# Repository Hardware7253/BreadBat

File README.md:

# BreadBat
A 3.3v breadbaord power supply that's powered by a single cell Li-Ion battery and uses USB-C for charging.
This design was made for prototyping portable devices on a breadboard.

I've had this designed manufactured and during testing I realised I forgot to consider the drop out voltage of the linear regulator. The battery charging and circuit protection seems to work fine, but the battery voltage isn't high enough for the LDO to reach a 3.3v output.

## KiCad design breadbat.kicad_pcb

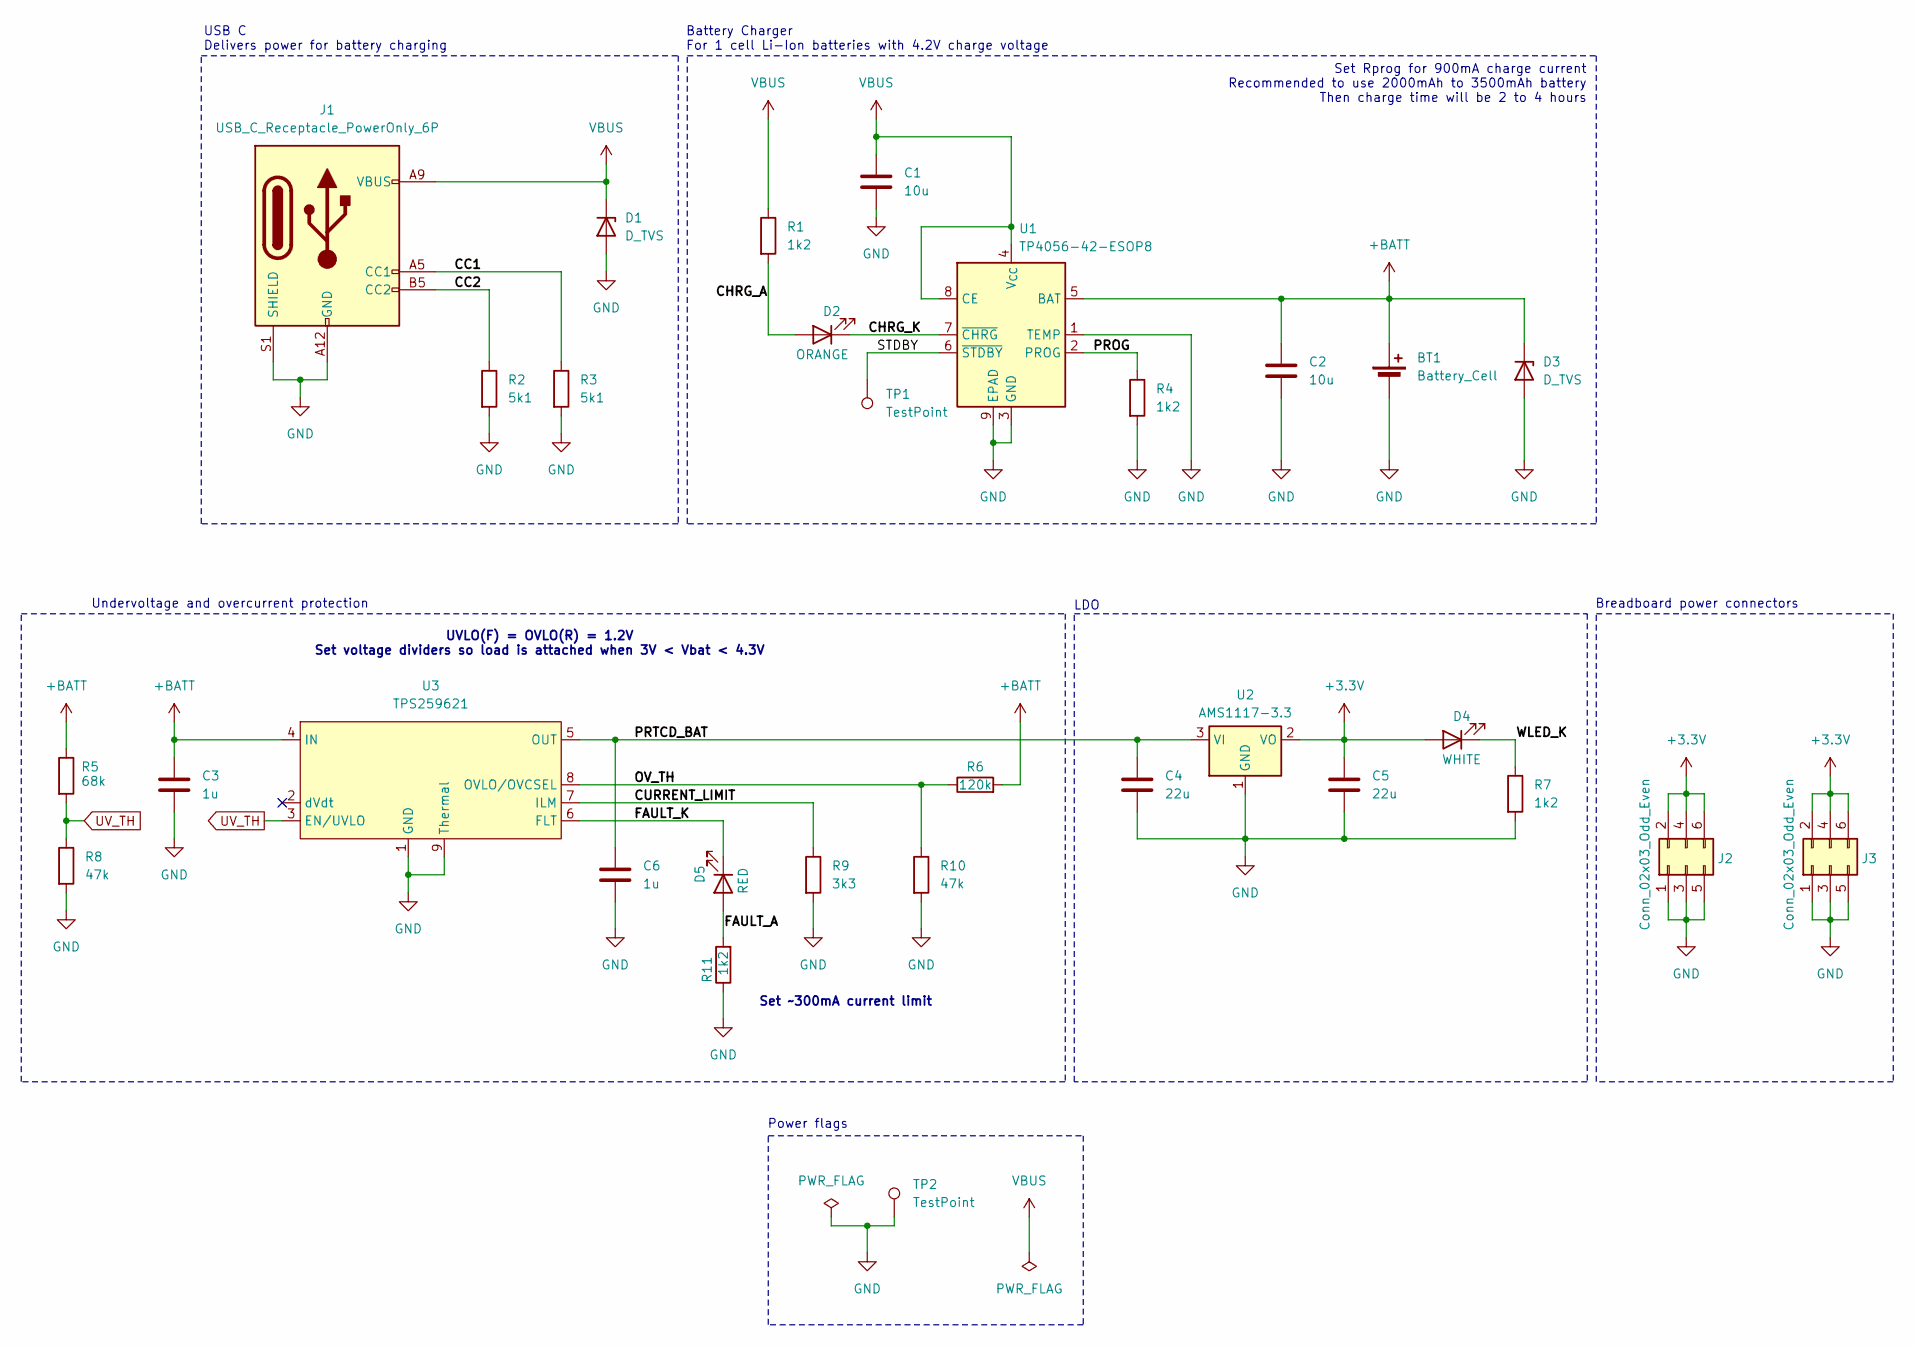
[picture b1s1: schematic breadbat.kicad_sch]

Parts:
BT1: Battery_Cell; JST_PH_B2B-PH-K_1x02_P2.00mm_Vertical; Part Number B2B-PH-K-S(LF)(SN); LCSC / JLC Part C131337
C1, C2: 10u; C_0603_1608Metric; Part Number CL10A106KP8NNNC; LCSC / JLC Part C19702
C3, C6: 1u; C_0603_1608Metric; Part Number CL10A105KB8NNNC; LCSC / JLC Part C15849
C4, C5: 22u; C_0805_2012Metric; Part Number CL21A226MAQNNNE; LCSC / JLC Part C45783
D1, D3: D_TVS; D_SOD-323_HandSoldering; Part Number WPE0731D3; LCSC / JLC Part C5143684
D2: ORANGE; LED_0603_1608Metric; Part Number KT-0603Y; LCSC / JLC Part C2287
D4: WHITE; LED_0603_1608Metric; Part Number KT-0603W; LCSC / JLC Part C2290
D5: RED; LED_0603_1608Metric; Part Number KT-0603R; LCSC / JLC Part C2286
J1: USB_C_Receptacle_PowerOnly_6P; USB_C_Receptacle_HRO_TYPE-C-31-M-17; Part Number YTC-TC6S-231; LCSC / JLC Part C2927302
J2, J3: Conn_02x03_Odd_Even; PinHeader_2x03_P2.54mm_Vertical; Part Number PZ254V-12-6P; LCSC / JLC Part C492420
R1, R4, R7, R11: 1k2; R_0603_1608Metric; Part Number 0603WAF1201T5E; LCSC / JLC Part C22765
R2, R3: 5k1; R_0603_1608Metric; Part Number 0603WAF5101T5E; LCSC / JLC Part C23186
R5: 68k; R_0603_1608Metric; Part Number 0603WAF6802T5E; LCSC / JLC Part C23231
R6: 120k; R_0603_1608Metric; Part Number 0603WAF1203T5E; LCSC / JLC Part C25808
R8, R10: 47k; R_0603_1608Metric; Part Number 0603WAF4702T5E; LCSC / JLC Part C25819
R9: 3k3; R_0603_1608Metric; Part Number 0603WAF3301T5E; LCSC / JLC Part C22978
TP1, TP2: TestPoint; TestPoint_Pad_D1.5mm
U1: TP4056-42-ESOP8; SOIC-8-1EP_3.9x4.9mm_P1.27mm_EP2.41x3.3mm_ThermalVias; Part Number TP4056-42-ESOP8; LCSC / JLC Part C16581
U2: AMS1117-3.3; SOT-223-3_TabPin2; Part Number AMS1117-3.3; LCSC / JLC Part C347222
U3: TPS259621; SOIC-8-1EP_3.9x4.9mm_P1.27mm_EP2.41x3.3mm_ThermalVias; Part Number TPS259621DDAR; LCSC / JLC Part C2155774

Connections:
+3.3V: C5.1, D4.2 (A), J2.2, J2.4, J2.6, J3.2, J3.4, J3.6, U2.2 (VO)
+BATT: BT1.1 (+), C2.1, C3.1, D3.1 (K), R5.1, R6.2, U1.5 (BAT), U3.4 (IN)
/CC1: J1.A5 (CC1), R3.1
/CC2: J1.B5 (CC2), R2.1
/CHRG_A: D2.2 (A), R1.2
/CHRG_K: D2.1 (K), U1.7 (~CHRG)
/CURRENT_LIMIT: R9.1, U3.7 (ILM)
/FAULT_A: D5.2 (A), R11.2
/FAULT_K: D5.1 (K), U3.6 (FLT)
/OV_TH: R6.1, R10.1, U3.8 (OVLO/OVCSEL)
/PROG: R4.1, U1.2 (PROG)
/PRTCD_BAT: C4.1, C6.1, U2.3 (VI), U3.5 (OUT)
/STDBY: TP1.1, U1.6 (~STDBY)
/WLED_K: D4.1 (K), R7.1
GND: BT1.2 (-), C1.2, C2.2, C3.2, C4.2, C5.2, C6.2, D1.2 (A), D3.2 (A), J1.A12 (GND), J1.B12 (GND), J1.S1 (SHIELD), J2.1, J2.3, J2.5, J3.1, J3.3, J3.5, R2.2, R3.2, R4.2, R7.2, R8.2, R9.2, R10.2, R11.1, TP2.1, U1.1 (TEMP), U1.3 (GND), U1.9 (EPAD), U2.1 (GND), U3.1 (GND), U3.9 (Thermal)
UV_TH: R5.2, R8.1, U3.3 (EN/UVLO)
VBUS: C1.1, D1.1 (K), J1.A9 (VBUS), J1.B9 (VBUS), R1.1, U1.4 (V_{CC}), U1.8 (CE)

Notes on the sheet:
LDO
Undervoltage and overcurrent protection
Power flags
UVLO(F) = OVLO(R) = 1.2V Set voltage dividers so load is attached when 3V < Vbat < 4.3V
Set ~300mA current limit
Breadboard power connectors
Set Rprog for 900mA charge current Recommended to use 2000mAh to 3500mAh battery Then charge time will be 2 to 4 hours
Battery Charger For 1 cell Li-Ion batteries with 4.2V charge voltage
USB C Delivers power for battery charging

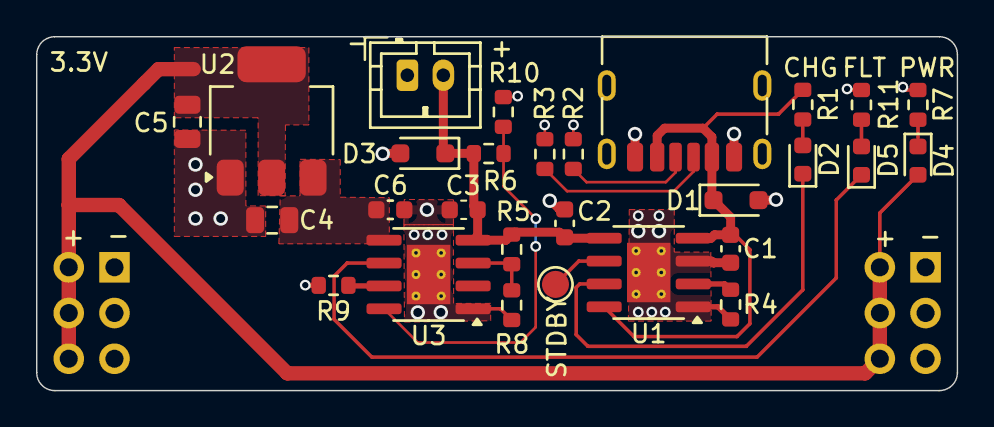
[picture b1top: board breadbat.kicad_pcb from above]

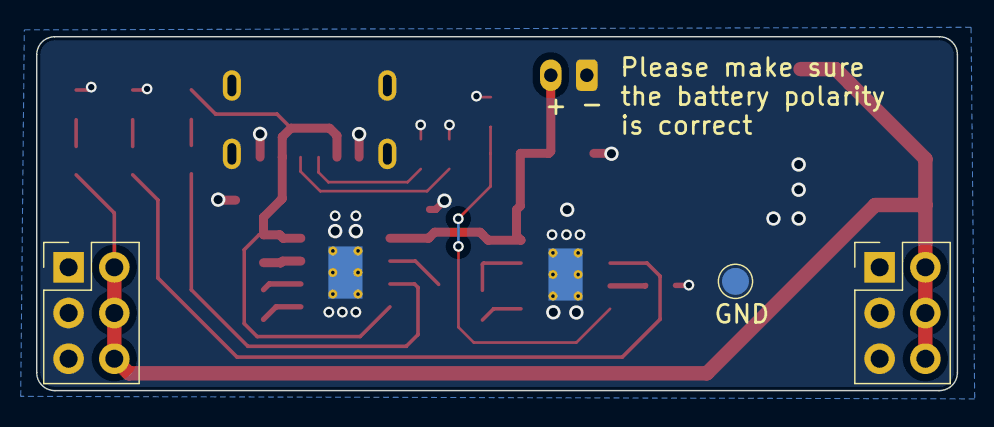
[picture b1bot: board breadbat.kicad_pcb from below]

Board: 2 copper layers, 51.2 x 19.7 mm, 31 parts (3 on the bottom side), 17 nets.

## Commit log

2025-05-19 Added README
    Added readme and added a BOM
